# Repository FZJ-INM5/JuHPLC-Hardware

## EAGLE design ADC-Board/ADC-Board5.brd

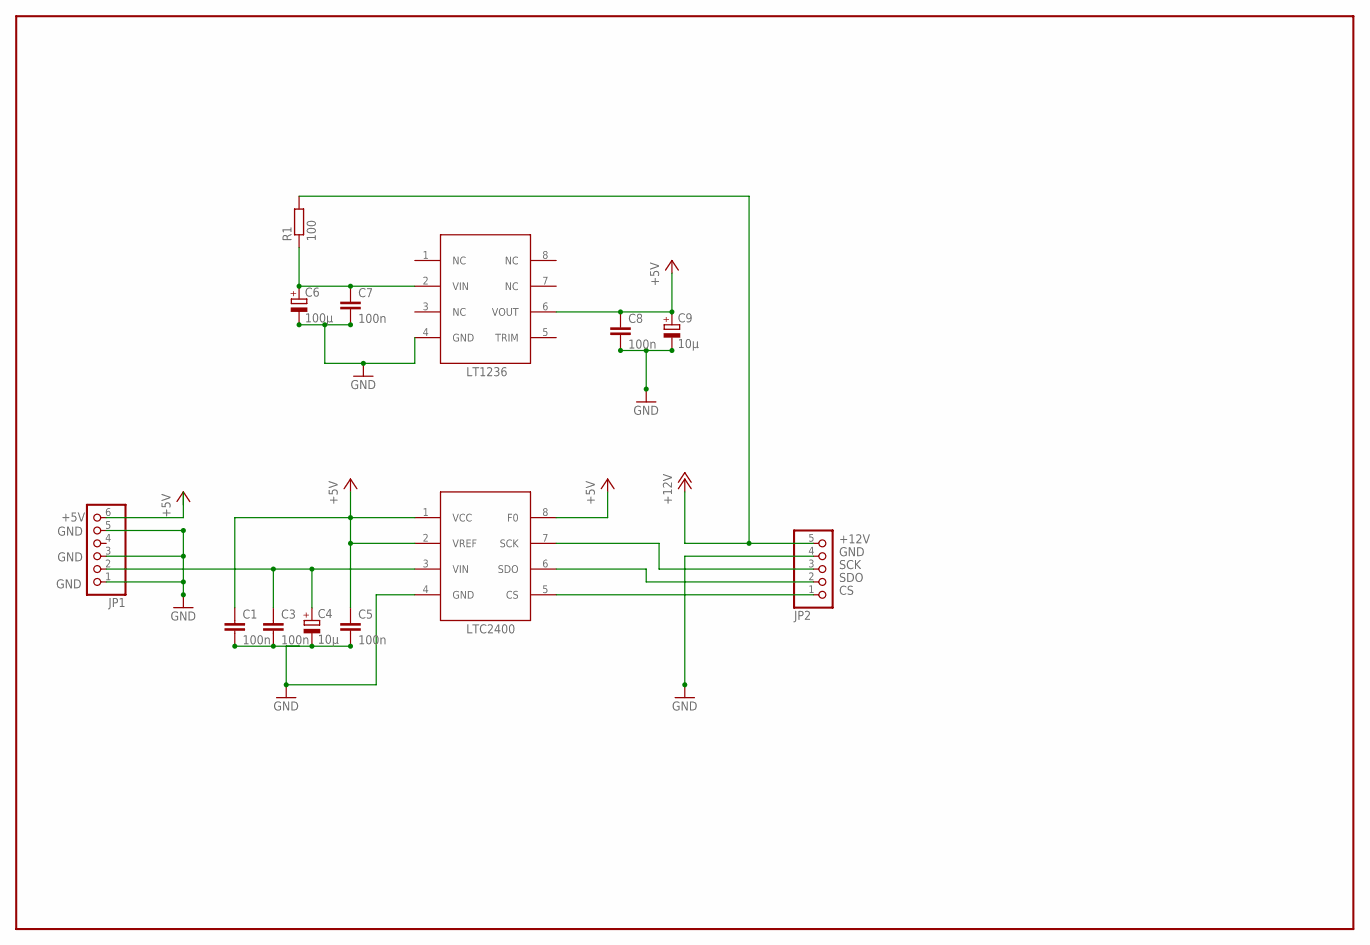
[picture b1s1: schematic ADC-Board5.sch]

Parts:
C1, C3, C5, C7, C8: 100n; C0805
C4, C9: 10µ; C/6032-28R
C6: 100µ; D/7343-31R
IC1: LT1236; SO08
IC2: LTC2400; SO08
JP1: PINHD-1X6; 1X06
JP2: PINHD-1X5; 1X05
R1: 100; M1206

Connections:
+5V: C1.1, C5.1, C8.1, C9.+, IC1.6 (VOUT), IC2.1 (VCC), IC2.2 (VREF), IC2.8 (F0), JP1.6
+12V: JP2.5, R1.2
CS: IC2.5 (CS), JP2.1
GND: C1.2, C3.2, C4.-, C5.2, C6.-, C7.2, C8.2, C9.-, IC1.4 (GND), IC2.4 (GND), JP1.1, JP1.3, JP1.5, JP2.4
unnamed: C3.1, C4.+, IC2.3 (VIN), JP1.2
unnamed: C6.+, C7.1, IC1.2 (VIN), R1.1
SCK: IC2.7 (SCK), JP2.3
SDO: IC2.6 (SDO), JP2.2

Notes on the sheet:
LT1236
LTC2400

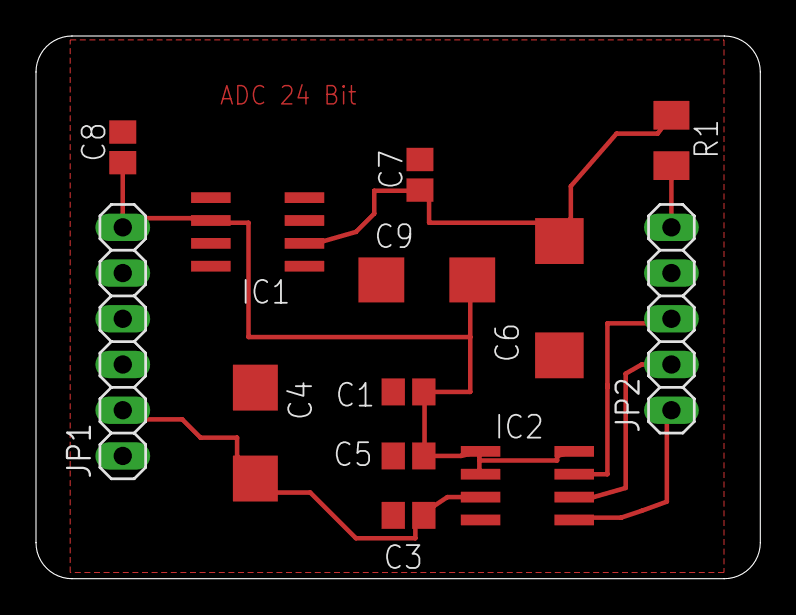
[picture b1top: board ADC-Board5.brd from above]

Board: 2 copper layers, 40.2 x 30.1 mm, 13 parts (0 on the bottom side), 8 nets.

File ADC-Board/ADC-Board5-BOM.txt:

Partlist

Exported from ADC-Board5.sch 

EAGLE Version 7.7.0 Copyright (c) 1988-2016 CadSoft

Assembly variant: 

Part     Value          Device            Package    

C1       100n           C-EUC0805         C0805      
C3       100n           C-EUC0805         C0805      
C4       10µ            CPOL-EUC/6032-28R C/6032-28R 
C5       100n           C-EUC0805         C0805      
C6       100µ           CPOL-EUD/7343-31R D/7343-31R 
C7       100n           C-EUC0805         C0805      
C8       100n           C-EUC0805         C0805      
C9       10µ            CPOL-EUC/6032-28R C/6032-28R 
IC1      LT1236         LT1236            SO08       
IC2      LTC2400        LTC2400           SO08       
JP1                     PINHD-1X6         1X06       
JP2                     PINHD-1X5         1X05       
R1       100            R-EU_M1206        M1206

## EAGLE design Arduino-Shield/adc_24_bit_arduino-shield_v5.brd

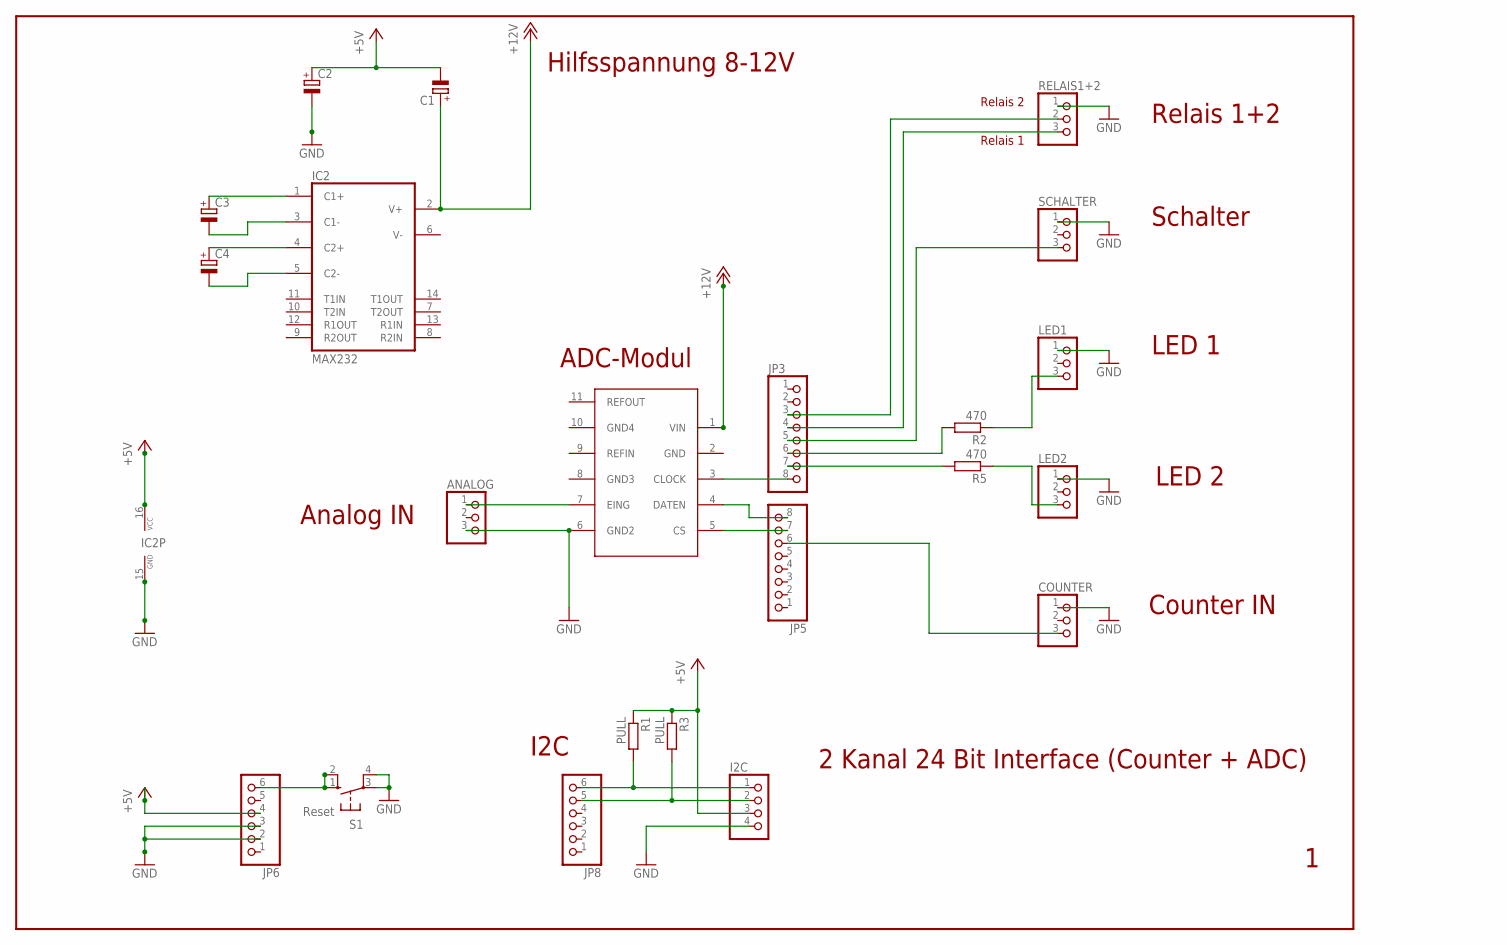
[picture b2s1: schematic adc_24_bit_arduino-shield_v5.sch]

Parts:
ANALOG: PINHD-1X3; 1X03
C1, C2, C3, C4: CPOL-EUE2-4; E2-4
COUNTER: PINHD-1X3; 1X03
I2C: PINHD-1X4; 1X04
IC1: MODUL; TEST
IC2: MAX232; DIL16
JP3, JP5: PINHD-1X8CLEANBIG; 1X08-CLEANBIG
JP6, JP8: PINHD-1X6CB; 1X06-CLEANBIG
LED1, LED2: PINHD-1X3; 1X03
R1, R3: PULL; 0207/15
R2, R5: 470; 0207/15
RELAIS1+2: PINHD-1X3; 1X03
S1: Reset; B3F-10XX
SCHALTER: PINHD-1X3; 1X03

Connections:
+5V: C1.-, C2.+, I2C.3, IC2.16 (VCC), JP6.4, R1.1, R3.1
+12V: C1.+, IC1.1 (VIN), IC2.2 (V+)
GND: ANALOG.3, C2.-, COUNTER.1, I2C.4, IC1.6 (GND2), IC2.15 (GND), JP6.2, JP6.3, LED1.1, LED2.1, RELAIS1+2.1, S1.3, S1.4 (P1), SCHALTER.1
unnamed: JP6.6, S1.1 (S), S1.2 (S1)
unnamed: IC1.3 (CLOCK), JP3.8
unnamed: IC1.4 (DATEN), JP5.8
unnamed: IC1.5 (CS), JP5.7
unnamed: ANALOG.1, IC1.7 (EING)
unnamed: C3.+, IC2.1 (C1+)
unnamed: C3.-, IC2.3 (C1-)
unnamed: C4.+, IC2.4 (C2+)
unnamed: C4.-, IC2.5 (C2-)
unnamed: COUNTER.3, JP5.6
unnamed: LED1.3, R2.1
unnamed: JP3.7, R5.2
unnamed: JP3.6, R2.2
unnamed: LED2.3, R5.1
unnamed: I2C.1, JP8.6, R1.2
unnamed: I2C.2, JP8.5, R3.2
unnamed: JP3.5, SCHALTER.3
unnamed: JP3.4, RELAIS1+2.3
unnamed: JP3.3, RELAIS1+2.2

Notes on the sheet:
2 Kanal 24 Bit Interface (Counter + ADC)
LED 2
Analog IN
Counter IN
LED 1
I2C
Schalter
Hilfsspannung 8-12V
ADC-Modul
Relais 1+2
Relais 2
Relais 1

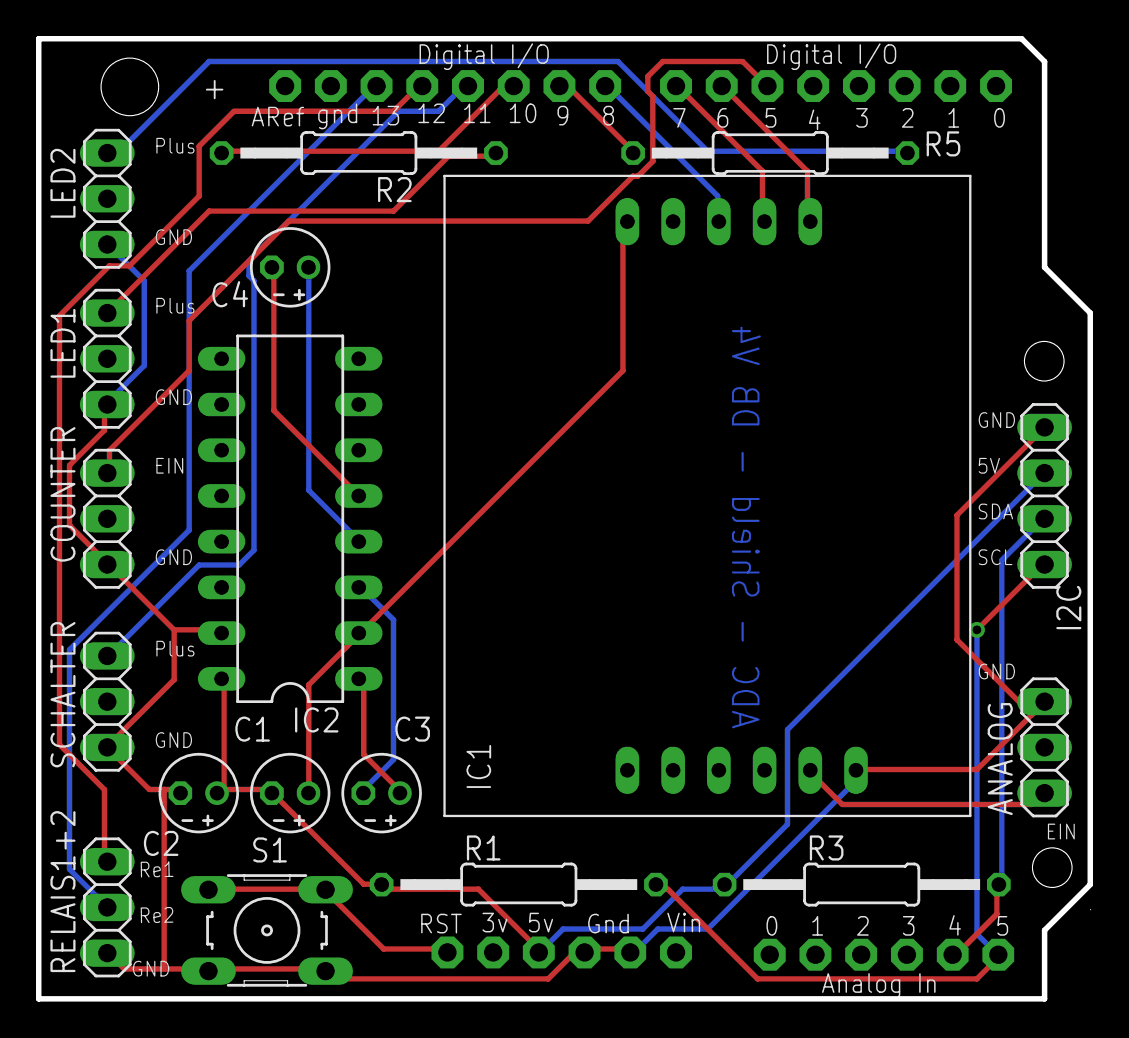
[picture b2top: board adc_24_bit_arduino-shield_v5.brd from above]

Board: 2 copper layers, 58.4 x 53.3 mm, 22 parts (0 on the bottom side), 22 nets.

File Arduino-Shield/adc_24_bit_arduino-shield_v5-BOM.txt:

Partlist

Exported from adc_24_bit_arduino-shield_v5.sch 

EAGLE Version 7.7.0 Copyright (c) 1988-2016 CadSoft

Assembly variant: 

Part      Value          Device            Package      

ANALOG                   PINHD-1X3         1X03         
C1                       CPOL-EUE2-4       E2-4          
C2                       CPOL-EUE2-4       E2-4         
C3                       CPOL-EUE2-4       E2-4          
C4                       CPOL-EUE2-4       E2-4         
COUNTER                  PINHD-1X3         1X03          
I2C                      PINHD-1X4         1X04          
IC1                      MODUL             TEST          
IC2       MAX232         MAX232            DIL16         
JP3                      PINHD-1X8CLEANBIG 1X08-CLEANBIG 
JP5                      PINHD-1X8CLEANBIG 1X08-CLEANBIG 
JP6                      PINHD-1X6CB       1X06-CLEANBIG 
JP8                      PINHD-1X6CB       1X06-CLEANBIG 
LED1                     PINHD-1X3         1X03          
LED2                     PINHD-1X3         1X03          
R1        PULL           R-EU_0207/15      0207/15       
R2        470            R-EU_0207/15      0207/15       
R3        PULL           R-EU_0207/15      0207/15       
R5        470            R-EU_0207/15      0207/15       
RELAIS1+2                PINHD-1X3         1X03          
S1        Reset          10-XX             B3F-10XX      
SCHALTER                 PINHD-1X3         1X03

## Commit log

2018-09-18 hardware files added
2018-09-18 Firmware added
2022-11-13 vorschlag zur Beschleunigung des Messungsstarts
